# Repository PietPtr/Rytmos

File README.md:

# Rytmos

Very much experimental software for defining, rendering, synthesizing, and practicing single voice music notation using embedded graphics (e.g. on an SSD1306 128x64 OLED display)

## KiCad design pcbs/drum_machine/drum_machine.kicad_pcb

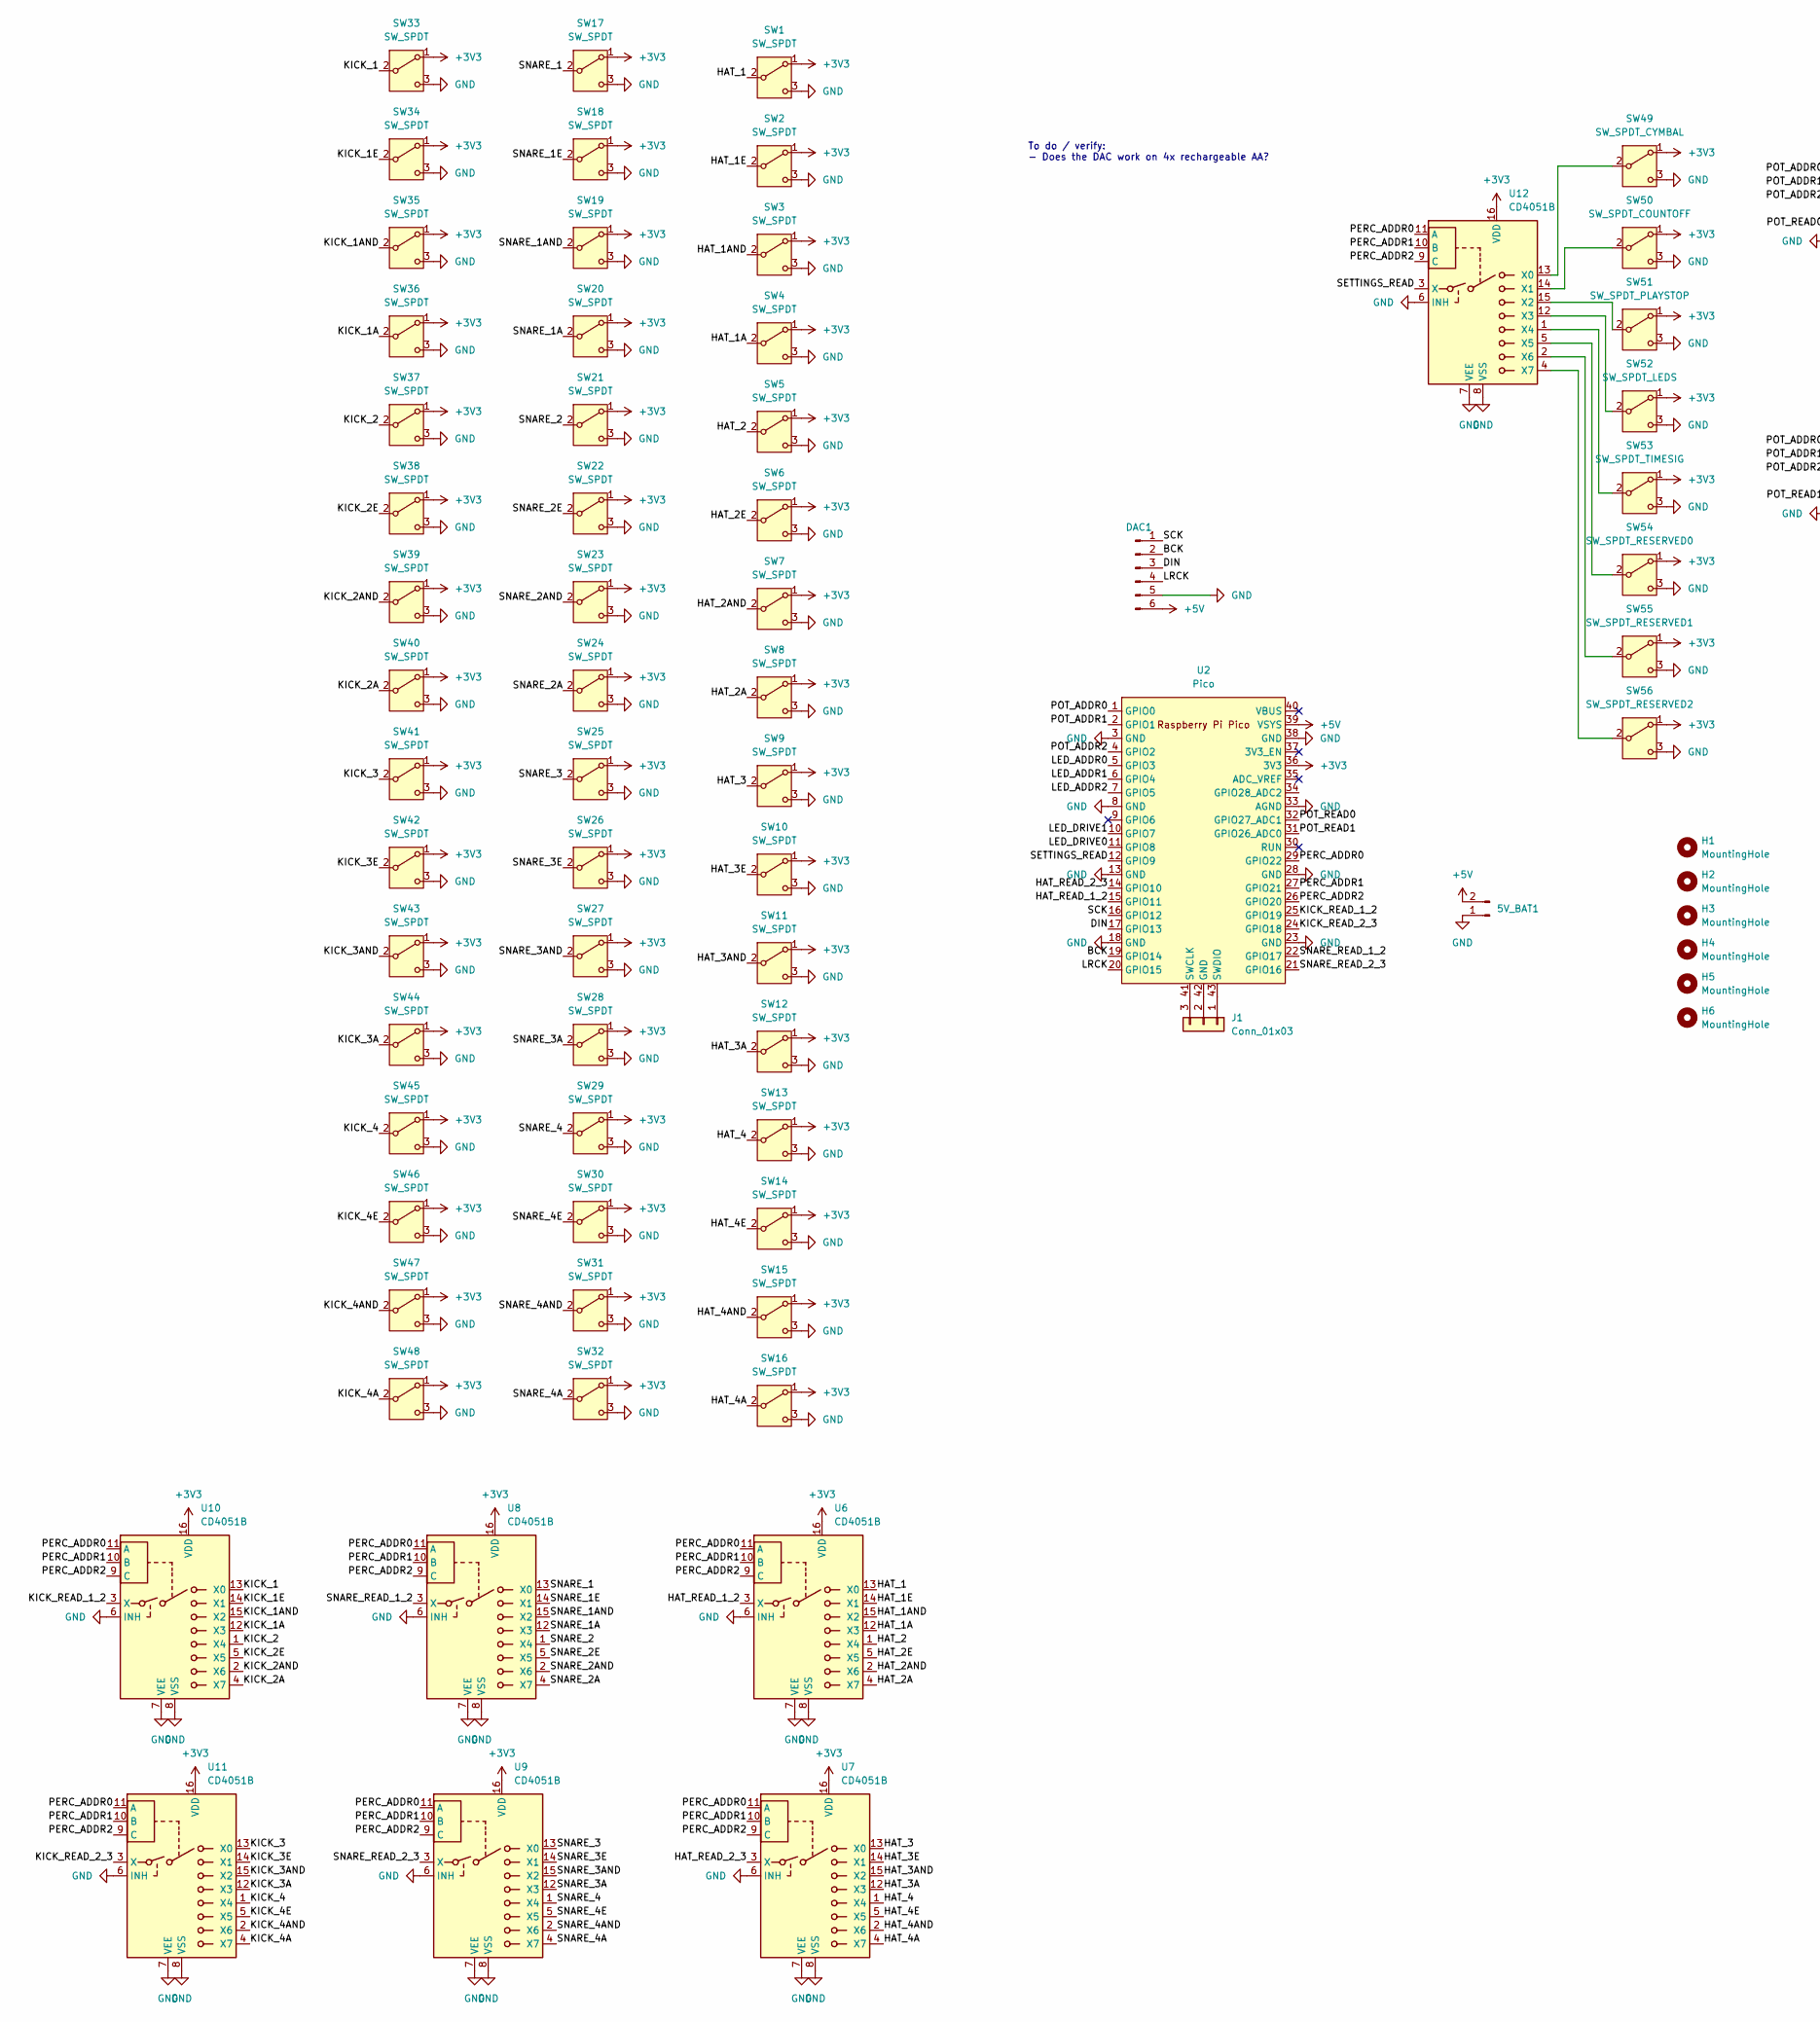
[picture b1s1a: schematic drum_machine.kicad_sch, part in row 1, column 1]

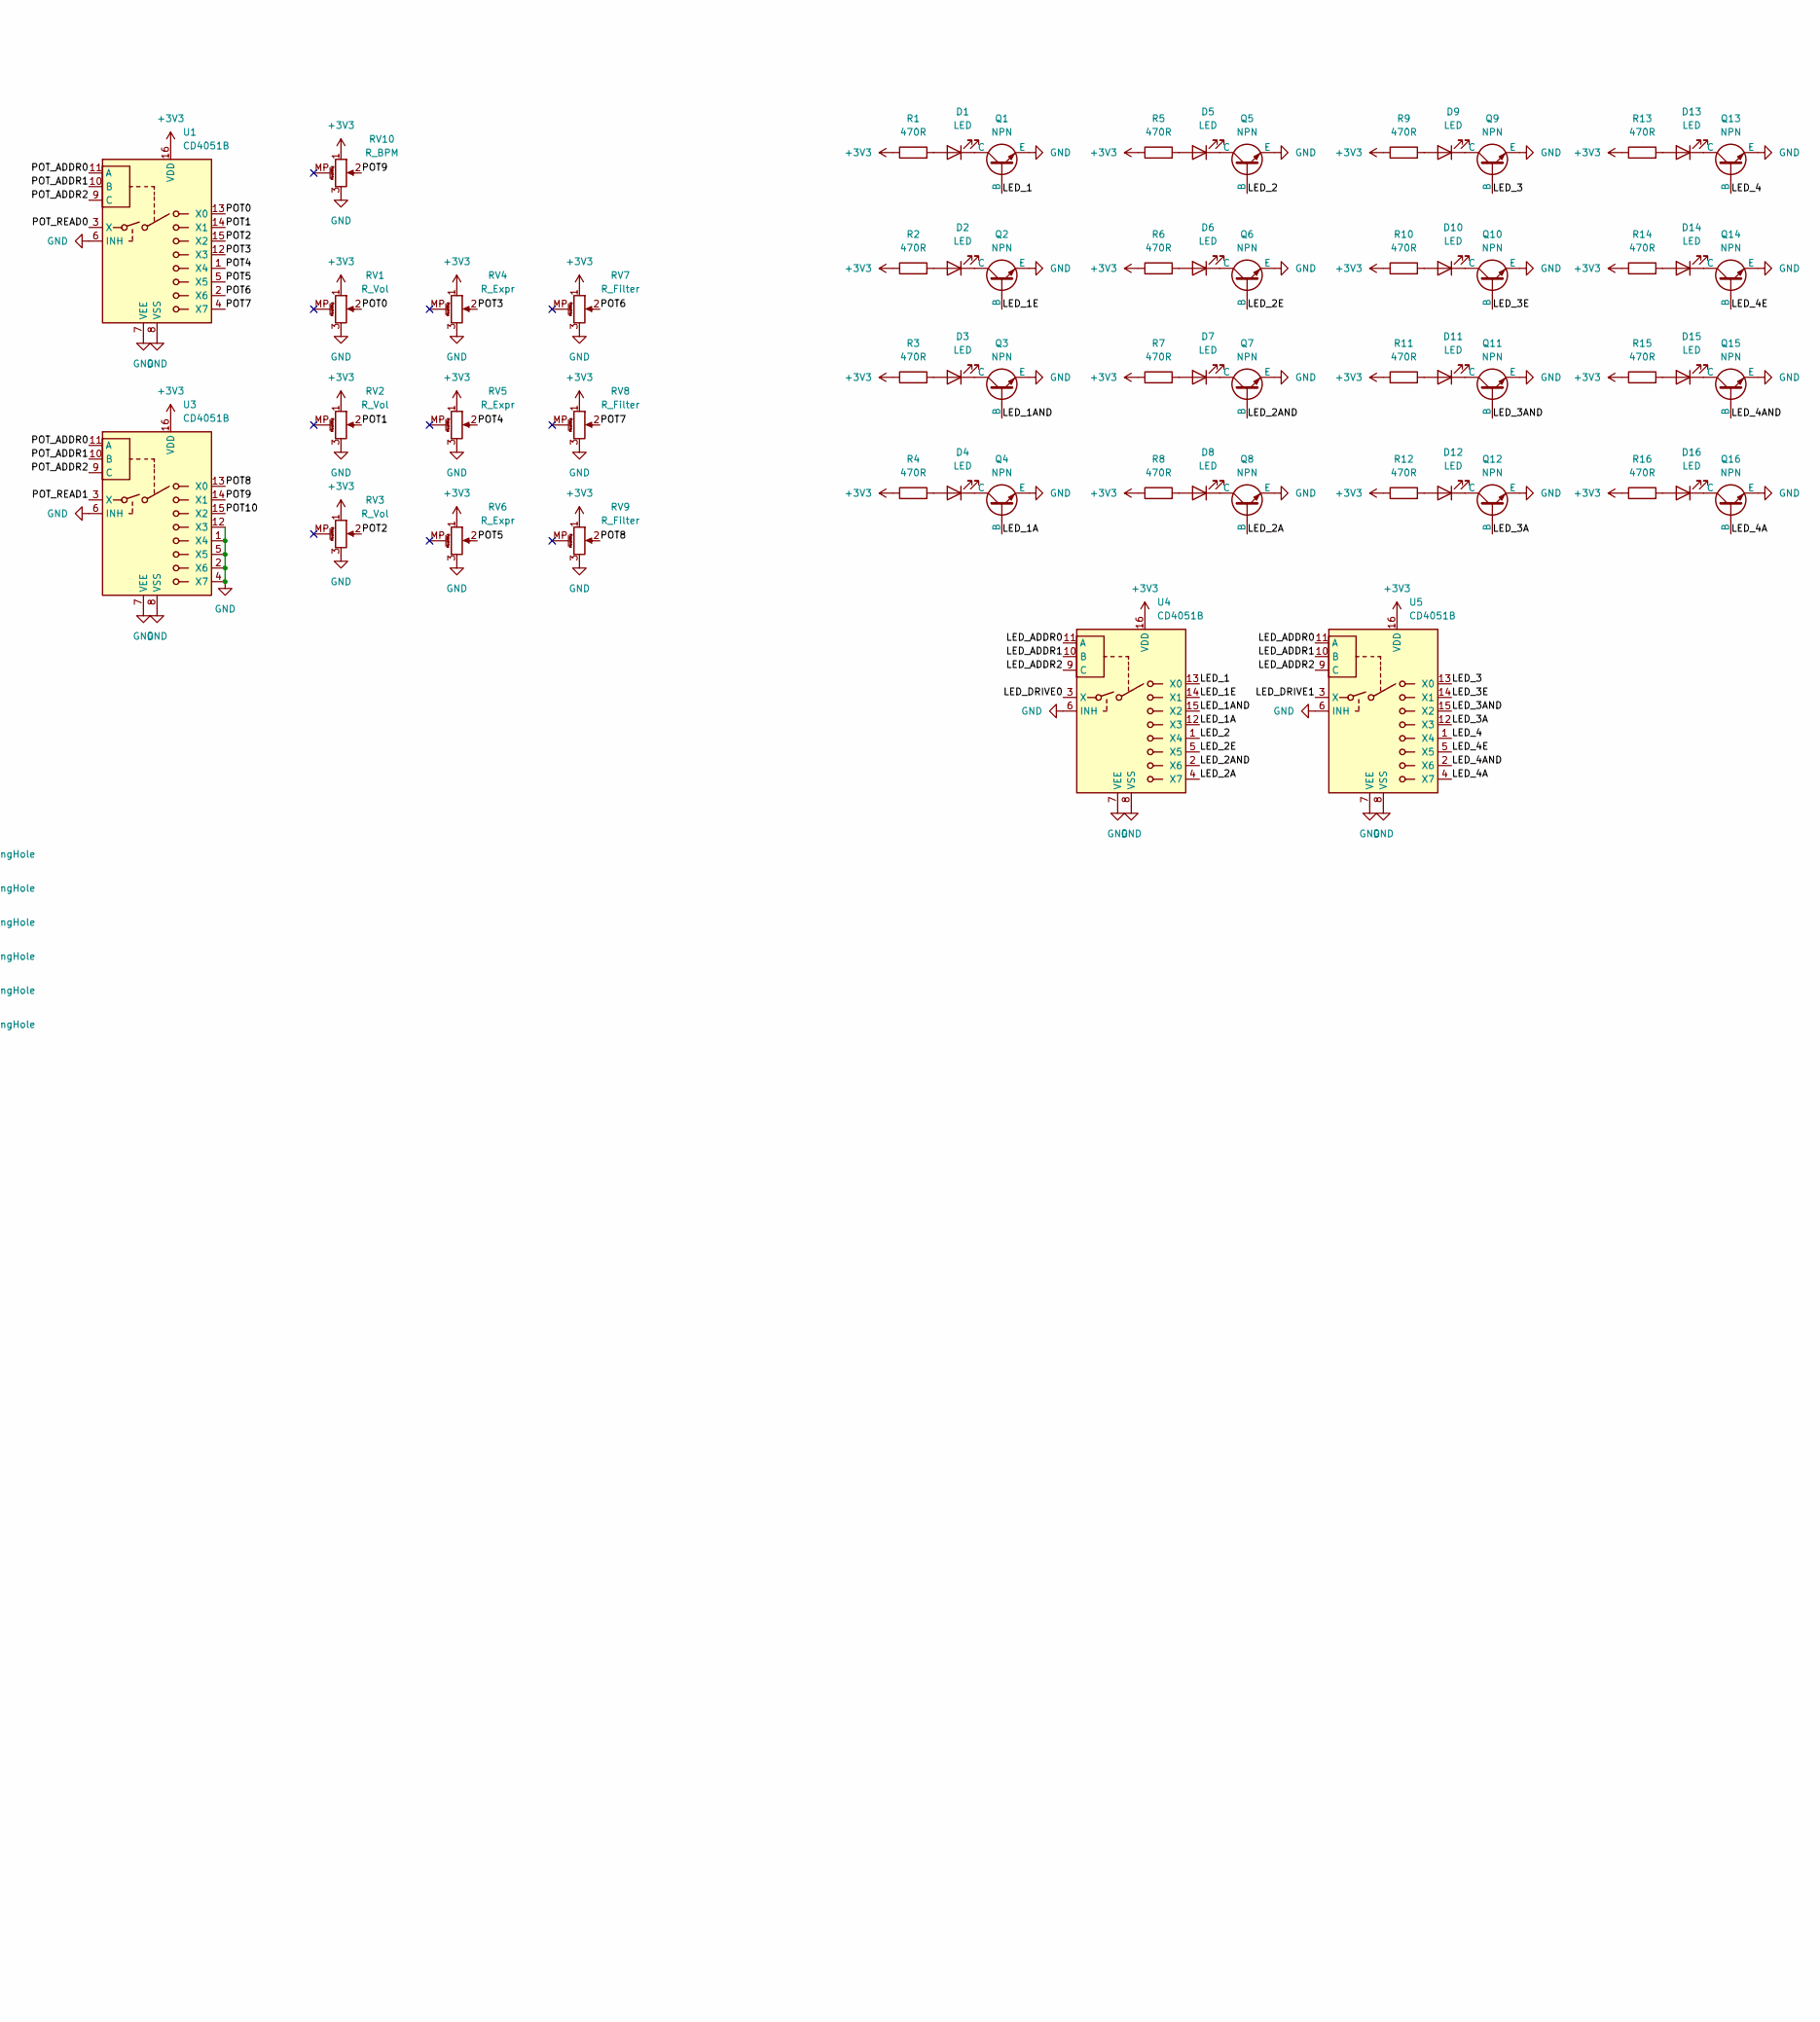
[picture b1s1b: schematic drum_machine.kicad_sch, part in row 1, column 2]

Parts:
5V_BAT1: Conn_01x02_Pin; PinSocket_1x02_P2.54mm_Vertical
D1, D2, D3, D4, D5, D6, D7, D8, D9, D10, D11, D12, D13, D14, D15, D16: LED; LED_D3.0mm
DAC1: DAC; PCM5102_BREAKOUT
H1, H2, H3, H4, H5, H6: MountingHole; MountingHole_2.7mm_M2.5
J1: Conn_01x03; PinSocket_1x03_P2.54mm_Vertical
Q1, Q2, Q3, Q4, Q5, Q6, Q7, Q8, Q9, Q10, Q11, Q12, Q13, Q14, Q15, Q16: NPN; TO-92L_Inline
R1, R2, R3, R4, R5, R6, R7, R8, R9, R10, R11, R12, R13, R14, R15, R16: 470R
RV1, RV2, RV3: R_Vol
RV4, RV5, RV6: R_Expr
RV7, RV8, RV9: R_Filter
RV10: R_BPM
SW1, SW2, SW3, SW4, SW5, SW6, SW7, SW8, SW9, SW10, SW11, SW12, SW13, SW14, SW15, SW16, SW17, SW18, SW19, SW20, SW21, SW22, SW23, SW24, SW25, SW26, SW27, SW28, SW29, SW30, SW31, SW32, SW33, SW34, SW35, SW36, SW37, SW38, SW39, SW40, SW41, SW42, SW43, SW44, SW45, SW46, SW47, SW48: SW_SPDT
SW49: SW_SPDT_CYMBAL
SW50: SW_SPDT_COUNTOFF
SW51: SW_SPDT_PLAYSTOP
SW52: SW_SPDT_LEDS
SW53: SW_SPDT_TIMESIG
SW54: SW_SPDT_RESERVED0
SW55: SW_SPDT_RESERVED1
SW56: SW_SPDT_RESERVED2
U1, U3, U4, U5, U6, U7, U8, U9, U10, U11, U12: CD4051B
U2: Pico; RPi_Pico_SMD_TH

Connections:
+3V3: R1.1, R2.1, R3.1, R4.1, R5.1, R6.1, R7.1, R8.1, R9.1, R10.1, R11.1, R12.1, R13.1, R14.1, R15.1, R16.1, RV1.1, RV2.1, RV3.1, RV4.1, RV5.1, RV6.1, RV7.1, RV8.1, RV9.1, RV10.1, SW1.1 (A), SW2.1 (A), SW3.1 (A), SW4.1 (A), SW5.1 (A), SW6.1 (A), SW7.1 (A), SW8.1 (A), SW9.1 (A), SW10.1 (A), SW11.1 (A), SW12.1 (A), SW13.1 (A), SW14.1 (A), SW15.1 (A), SW16.1 (A), SW17.1 (A), SW18.1 (A), SW19.1 (A), SW20.1 (A), SW21.1 (A), SW22.1 (A), SW23.1 (A), SW24.1 (A), SW25.1 (A), SW26.1 (A), SW27.1 (A), SW28.1 (A), SW29.1 (A), SW30.1 (A), SW31.1 (A), SW32.1 (A), SW33.1 (A), SW34.1 (A), SW35.1 (A), SW36.1 (A), SW37.1 (A), SW38.1 (A), SW39.1 (A), SW40.1 (A), SW41.1 (A), SW42.1 (A), SW43.1 (A), SW44.1 (A), SW45.1 (A), SW46.1 (A), SW47.1 (A), SW48.1 (A), SW49.1 (A), SW50.1 (A), SW51.1 (A), SW52.1 (A), SW53.1 (A), SW54.1 (A), SW55.1 (A), SW56.1 (A), U1.16 (VDD), U2.36 (3V3), U3.16 (VDD), U4.16 (VDD), U5.16 (VDD), U6.16 (VDD), U7.16 (VDD), U8.16 (VDD), U9.16 (VDD), U10.16 (VDD), U11.16 (VDD), U12.16 (VDD)
+5V: 5V_BAT1.2, DAC1.6, U2.39 (VSYS)
/BCK: DAC1.2, U2.19 (GPIO14)
/DIN: DAC1.3, U2.17 (GPIO13)
/HAT_1: SW1.2 (B), U6.13 (X0)
/HAT_1A: SW4.2 (B), U6.12 (X3)
/HAT_1AND: SW3.2 (B), U6.15 (X2)
/HAT_1E: SW2.2 (B), U6.14 (X1)
/HAT_2: SW5.2 (B), U6.1 (X4)
/HAT_2A: SW8.2 (B), U6.4 (X7)
/HAT_2AND: SW7.2 (B), U6.2 (X6)
/HAT_2E: SW6.2 (B), U6.5 (X5)
/HAT_3: SW9.2 (B), U7.13 (X0)
/HAT_3A: SW12.2 (B), U7.12 (X3)
/HAT_3AND: SW11.2 (B), U7.15 (X2)
/HAT_3E: SW10.2 (B), U7.14 (X1)
/HAT_4: SW13.2 (B), U7.1 (X4)
/HAT_4A: SW16.2 (B), U7.4 (X7)
/HAT_4AND: SW15.2 (B), U7.2 (X6)
/HAT_4E: SW14.2 (B), U7.5 (X5)
/HAT_READ_1_2: U2.15 (GPIO11), U6.3 (X)
/HAT_READ_2_3: U2.14 (GPIO10), U7.3 (X)
/KICK_1: SW33.2 (B), U10.13 (X0)
/KICK_1A: SW36.2 (B), U10.12 (X3)
/KICK_1AND: SW35.2 (B), U10.15 (X2)
/KICK_1E: SW34.2 (B), U10.14 (X1)
/KICK_2: SW37.2 (B), U10.1 (X4)
/KICK_2A: SW40.2 (B), U10.4 (X7)
/KICK_2AND: SW39.2 (B), U10.2 (X6)
/KICK_2E: SW38.2 (B), U10.5 (X5)
/KICK_3: SW41.2 (B), U11.13 (X0)
/KICK_3A: SW44.2 (B), U11.12 (X3)
/KICK_3AND: SW43.2 (B), U11.15 (X2)
/KICK_3E: SW42.2 (B), U11.14 (X1)
/KICK_4: SW45.2 (B), U11.1 (X4)
/KICK_4A: SW48.2 (B), U11.4 (X7)
/KICK_4AND: SW47.2 (B), U11.2 (X6)
/KICK_4E: SW46.2 (B), U11.5 (X5)
/KICK_READ_1_2: U2.25 (GPIO19), U10.3 (X)
/KICK_READ_2_3: U2.24 (GPIO18), U11.3 (X)
/LED_1: Q1.2 (B), U4.13 (X0)
/LED_1A: Q4.2 (B), U4.12 (X3)
/LED_1AND: Q3.2 (B), U4.15 (X2)
/LED_1E: Q2.2 (B), U4.14 (X1)
/LED_2: Q5.2 (B), U4.1 (X4)
/LED_2A: Q8.2 (B), U4.4 (X7)
/LED_2AND: Q7.2 (B), U4.2 (X6)
/LED_2E: Q6.2 (B), U4.5 (X5)
/LED_3: Q9.2 (B), U5.13 (X0)
/LED_3A: Q12.2 (B), U5.12 (X3)
/LED_3AND: Q11.2 (B), U5.15 (X2)
/LED_3E: Q10.2 (B), U5.14 (X1)
/LED_4: Q13.2 (B), U5.1 (X4)
/LED_4A: Q16.2 (B), U5.4 (X7)
/LED_4AND: Q15.2 (B), U5.2 (X6)
/LED_4E: Q14.2 (B), U5.5 (X5)
/LED_ADDR0: U2.5 (GPIO3), U4.11 (A), U5.11 (A)
/LED_ADDR1: U2.6 (GPIO4), U4.10 (B), U5.10 (B)
/LED_ADDR2: U2.7 (GPIO5), U4.9 (C), U5.9 (C)
/LED_DRIVE0: U2.11 (GPIO8), U4.3 (X)
/LED_DRIVE1: U2.10 (GPIO7), U5.3 (X)
/LRCK: DAC1.4, U2.20 (GPIO15)
/PERC_ADDR0: U2.29 (GPIO22), U6.11 (A), U7.11 (A), U8.11 (A), U9.11 (A), U10.11 (A), U11.11 (A), U12.11 (A)
/PERC_ADDR1: U2.27 (GPIO21), U6.10 (B), U7.10 (B), U8.10 (B), U9.10 (B), U10.10 (B), U11.10 (B), U12.10 (B)
/PERC_ADDR2: U2.26 (GPIO20), U6.9 (C), U7.9 (C), U8.9 (C), U9.9 (C), U10.9 (C), U11.9 (C), U12.9 (C)
/POT0: RV1.2, U1.13 (X0)
/POT1: RV2.2, U1.14 (X1)
/POT2: RV3.2, U1.15 (X2)
/POT3: RV4.2, U1.12 (X3)
/POT4: RV5.2, U1.1 (X4)
/POT5: RV6.2, U1.5 (X5)
/POT6: RV7.2, U1.2 (X6)
/POT7: RV8.2, U1.4 (X7)
/POT8: RV9.2, U3.13 (X0)
/POT9: RV10.2, U3.14 (X1)
/POT10: U3.15 (X2)
/POT_ADDR0: U1.11 (A), U2.1 (GPIO0), U3.11 (A)
/POT_ADDR1: U1.10 (B), U2.2 (GPIO1), U3.10 (B)
/POT_ADDR2: U1.9 (C), U2.4 (GPIO2), U3.9 (C)
/POT_READ0: U1.3 (X), U2.32 (GPIO27_ADC1)
/POT_READ1: U2.31 (GPIO26_ADC0), U3.3 (X)
/SCK: DAC1.1, U2.16 (GPIO12)
/SETTINGS_READ: U2.12 (GPIO9), U12.3 (X)
/SNARE_1: SW17.2 (B), U8.13 (X0)
/SNARE_1A: SW20.2 (B), U8.12 (X3)
/SNARE_1AND: SW19.2 (B), U8.15 (X2)
/SNARE_1E: SW18.2 (B), U8.14 (X1)
/SNARE_2: SW21.2 (B), U8.1 (X4)
/SNARE_2A: SW24.2 (B), U8.4 (X7)
/SNARE_2AND: SW23.2 (B), U8.2 (X6)
/SNARE_2E: SW22.2 (B), U8.5 (X5)
/SNARE_3: SW25.2 (B), U9.13 (X0)
/SNARE_3A: SW28.2 (B), U9.12 (X3)
/SNARE_3AND: SW27.2 (B), U9.15 (X2)
/SNARE_3E: SW26.2 (B), U9.14 (X1)
/SNARE_4: SW29.2 (B), U9.1 (X4)
/SNARE_4A: SW32.2 (B), U9.4 (X7)
/SNARE_4AND: SW31.2 (B), U9.2 (X6)
/SNARE_4E: SW30.2 (B), U9.5 (X5)
/SNARE_READ_1_2: U2.22 (GPIO17), U8.3 (X)
/SNARE_READ_2_3: U2.21 (GPIO16), U9.3 (X)
GND: 5V_BAT1.1, DAC1.5, Q1.3 (E), Q2.3 (E), Q3.3 (E), Q4.3 (E), Q5.3 (E), Q6.3 (E), Q7.3 (E), Q8.3 (E), Q9.3 (E), Q10.3 (E), Q11.3 (E), Q12.3 (E), Q13.3 (E), Q14.3 (E), Q15.3 (E), Q16.3 (E), RV1.3, RV2.3, RV3.3, RV4.3, RV5.3, RV6.3, RV7.3, RV8.3, RV9.3, RV10.3, SW1.3 (C), SW2.3 (C), SW3.3 (C), SW4.3 (C), SW5.3 (C), SW6.3 (C), SW7.3 (C), SW8.3 (C), SW9.3 (C), SW10.3 (C), SW11.3 (C), SW12.3 (C), SW13.3 (C), SW14.3 (C), SW15.3 (C), SW16.3 (C), SW17.3 (C), SW18.3 (C), SW19.3 (C), SW20.3 (C), SW21.3 (C), SW22.3 (C), SW23.3 (C), SW24.3 (C), SW25.3 (C), SW26.3 (C), SW27.3 (C), SW28.3 (C), SW29.3 (C), SW30.3 (C), SW31.3 (C), SW32.3 (C), SW33.3 (C), SW34.3 (C), SW35.3 (C), SW36.3 (C), SW37.3 (C), SW38.3 (C), SW39.3 (C), SW40.3 (C), SW41.3 (C), SW42.3 (C), SW43.3 (C), SW44.3 (C), SW45.3 (C), SW46.3 (C), SW47.3 (C), SW48.3 (C), SW49.3 (C), SW50.3 (C), SW51.3 (C), SW52.3 (C), SW53.3 (C), SW54.3 (C), SW55.3 (C), SW56.3 (C), U1.6 (INH), U1.7 (VEE), U1.8 (VSS), U2.3 (GND), U2.8 (GND), U2.13 (GND), U2.18 (GND), U2.23 (GND), U2.28 (GND), U2.33 (AGND), U2.38 (GND), U3.1 (X4), U3.2 (X6), U3.4 (X7), U3.5 (X5), U3.6 (INH), U3.7 (VEE), U3.8 (VSS), U3.12 (X3), U4.6 (INH), U4.7 (VEE), U4.8 (VSS), U5.6 (INH), U5.7 (VEE), U5.8 (VSS), U6.6 (INH), U6.7 (VEE), U6.8 (VSS), U7.6 (INH), U7.7 (VEE), U7.8 (VSS), U8.6 (INH), U8.7 (VEE), U8.8 (VSS), U9.6 (INH), U9.7 (VEE), U9.8 (VSS), U10.6 (INH), U10.7 (VEE), U10.8 (VSS), U11.6 (INH), U11.7 (VEE), U11.8 (VSS), U12.6 (INH), U12.7 (VEE), U12.8 (VSS)
unnamed: D1.2 (A), R1.2
unnamed: D1.1 (K), Q1.1 (C)
unnamed: D2.2 (A), R2.2
unnamed: D2.1 (K), Q2.1 (C)
unnamed: D3.2 (A), R3.2
unnamed: D3.1 (K), Q3.1 (C)
unnamed: D4.2 (A), R4.2
unnamed: D4.1 (K), Q4.1 (C)
unnamed: D5.2 (A), R5.2
unnamed: D5.1 (K), Q5.1 (C)
unnamed: D6.2 (A), R6.2
unnamed: D6.1 (K), Q6.1 (C)
unnamed: D7.2 (A), R7.2
unnamed: D7.1 (K), Q7.1 (C)
unnamed: D8.2 (A), R8.2
unnamed: D8.1 (K), Q8.1 (C)
unnamed: D9.2 (A), R9.2
unnamed: D9.1 (K), Q9.1 (C)
unnamed: D10.2 (A), R10.2
unnamed: D10.1 (K), Q10.1 (C)
unnamed: D11.2 (A), R11.2
unnamed: D11.1 (K), Q11.1 (C)
unnamed: D12.2 (A), R12.2
unnamed: D12.1 (K), Q12.1 (C)
unnamed: D13.2 (A), R13.2
unnamed: D13.1 (K), Q13.1 (C)
unnamed: D14.2 (A), R14.2
unnamed: D14.1 (K), Q14.1 (C)
unnamed: D15.2 (A), R15.2
unnamed: D15.1 (K), Q15.1 (C)
unnamed: D16.2 (A), R16.2
unnamed: D16.1 (K), Q16.1 (C)
unnamed: J1.1, U2.43 (SWDIO)
unnamed: J1.2, U2.42 (GND)
unnamed: J1.3, U2.41 (SWCLK)
unnamed: SW49.2 (B), U12.13 (X0)
unnamed: SW50.2 (B), U12.14 (X1)
unnamed: SW51.2 (B), U12.15 (X2)
unnamed: SW52.2 (B), U12.12 (X3)
unnamed: SW53.2 (B), U12.1 (X4)
unnamed: SW54.2 (B), U12.5 (X5)
unnamed: SW55.2 (B), U12.2 (X6)
unnamed: SW56.2 (B), U12.4 (X7)

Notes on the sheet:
To do / verify: - Does the DAC work on 4x rechargeable AA?

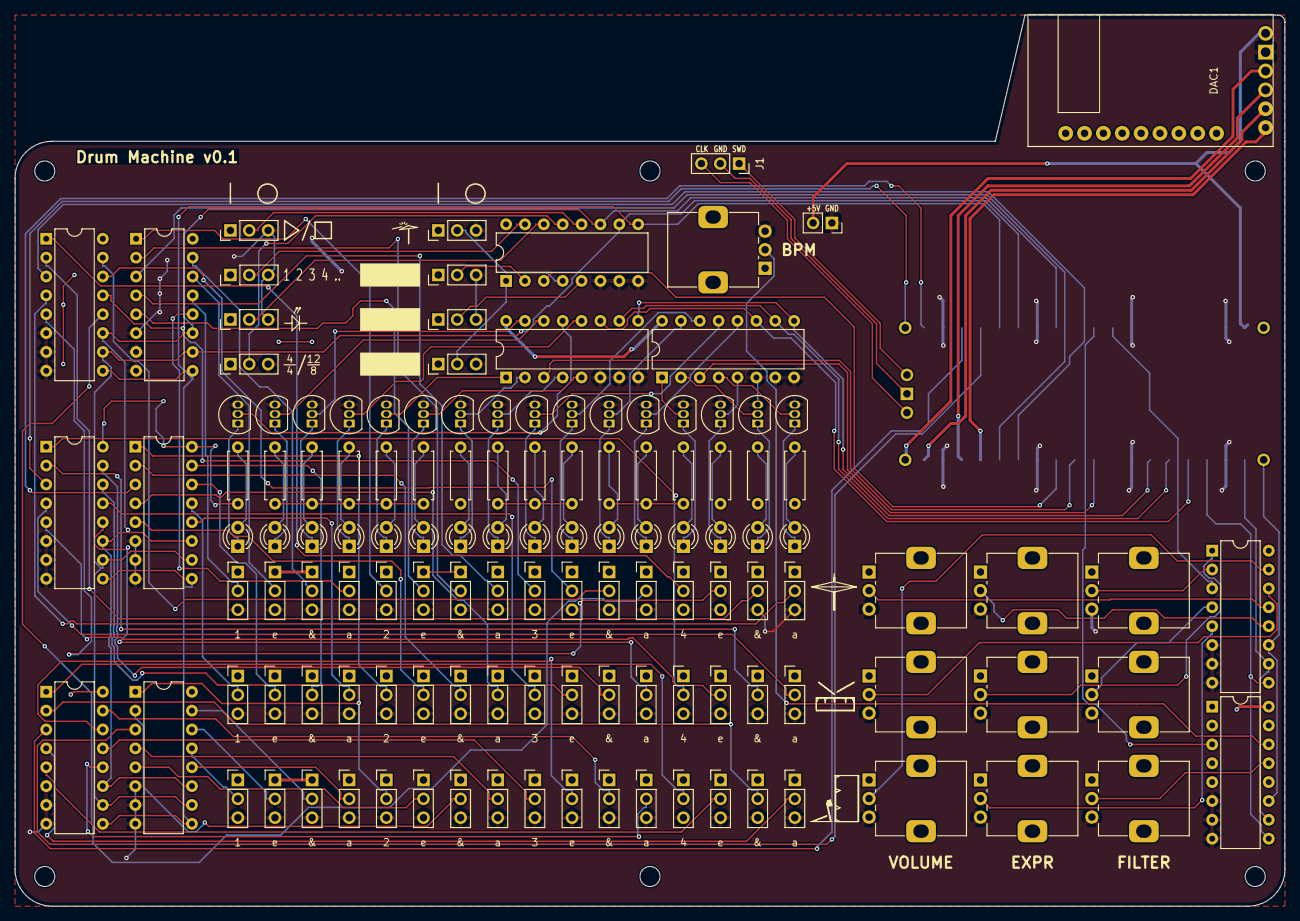
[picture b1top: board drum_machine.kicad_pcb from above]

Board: 2 copper layers, 171.0 x 120.0 mm, 135 parts (1 on the bottom side), 144 nets.

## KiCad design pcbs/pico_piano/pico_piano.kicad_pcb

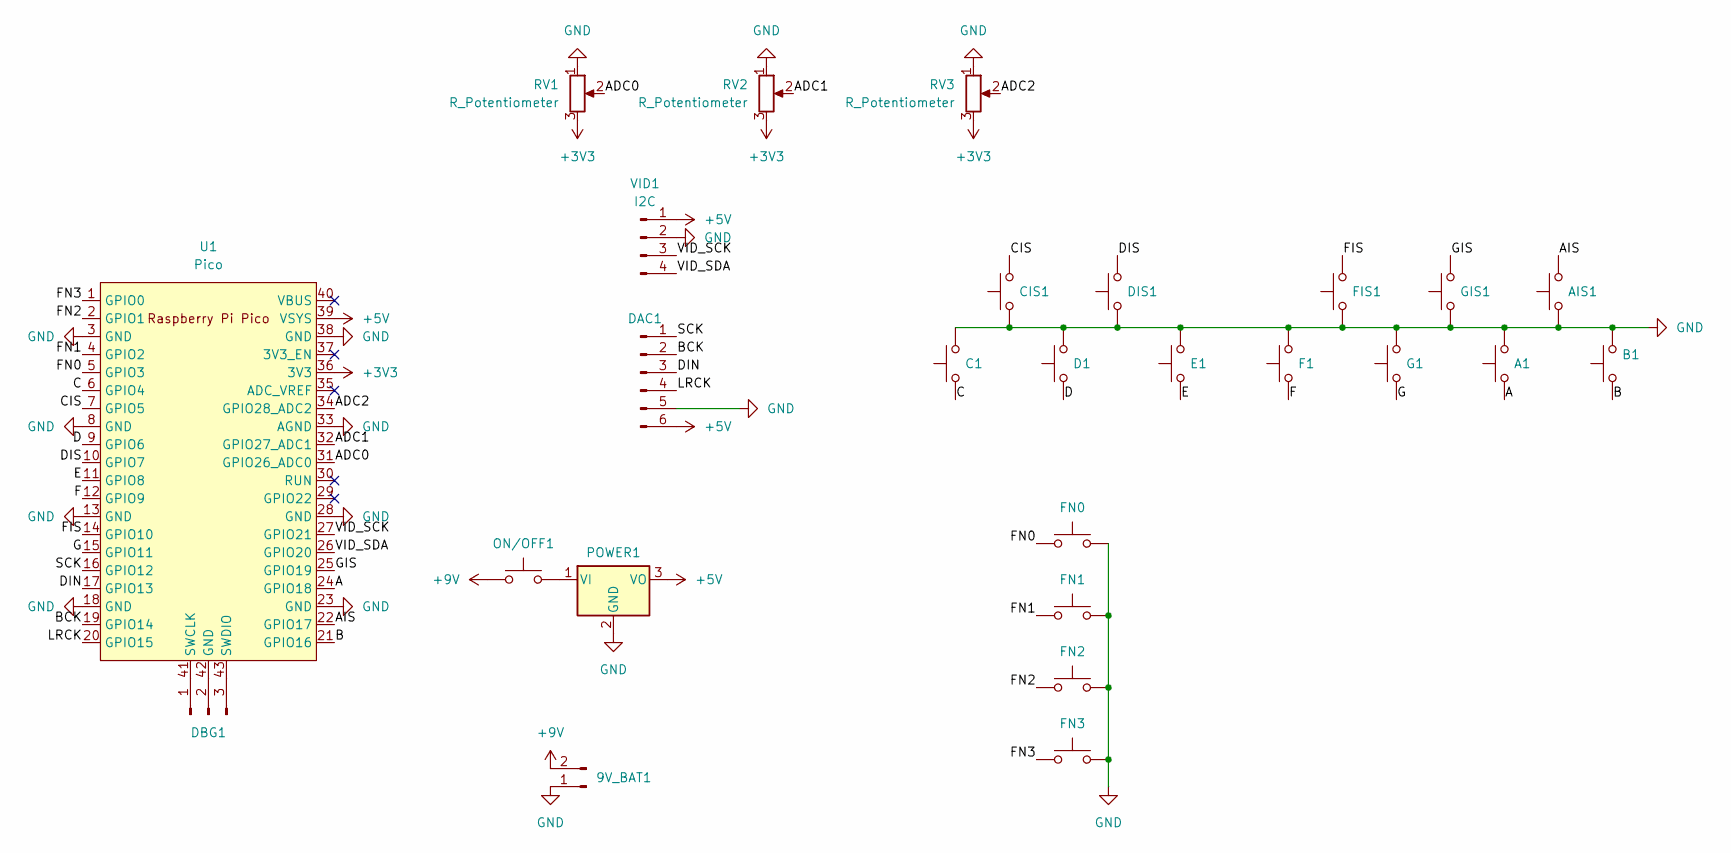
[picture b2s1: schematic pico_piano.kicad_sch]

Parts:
9V_BAT1: Conn_01x02_Pin; PinSocket_1x02_P2.54mm_Vertical
A1: SW_Push; KAILH_MUTE
AIS1: SW_Push; KAILH_MUTE
B1: SW_Push; KAILH_MUTE
C1: SW_Push; KAILH_MUTE
CIS1: SW_Push; KAILH_MUTE
D1: SW_Push; KAILH_MUTE
DAC1: DAC; PCM5102_BREAKOUT
DBG1: Conn_01x03_Pin; PinSocket_1x03_P2.54mm_Vertical
DIS1: SW_Push; KAILH_MUTE
E1: SW_Push; KAILH_MUTE
F1: SW_Push; KAILH_MUTE
FIS1: SW_Push; KAILH_MUTE
FN0, FN1, FN2, FN3: SW_Push; KAILH_MUTE
G1: SW_Push; KAILH_MUTE
GIS1: SW_Push; KAILH_MUTE
ON/OFF1: SW_Push; PinHeader_1x03_P2.54mm_Vertical
POWER1: LM7805_TO220; TO-220-3_Horizontal_TabDown
RV1, RV2, RV3: R_Potentiometer; PinHeader_1x03_P2.54mm_Vertical
U1: Pico; RPi_Pico_SMD_TH
VID1: I2C; PinHeader_1x04_P2.54mm_Vertical

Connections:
+3V3: RV1.3, RV2.3, RV3.3, U1.36 (3V3)
+5V: DAC1.6, POWER1.3 (VO), U1.39 (VSYS), VID1.1
+9V: 9V_BAT1.2, ON/OFF1.1
/A: A1.1, U1.24 (GPIO18)
/ADC0: RV1.2, U1.31 (GPIO26_ADC0)
/ADC1: RV2.2, U1.32 (GPIO27_ADC1)
/ADC2: RV3.2, U1.34 (GPIO28_ADC2)
/AIS: AIS1.2, U1.22 (GPIO17)
/B: B1.1, U1.21 (GPIO16)
/BCK: DAC1.2, U1.19 (GPIO14)
/C: C1.1, U1.6 (GPIO4)
/CIS: CIS1.2, U1.7 (GPIO5)
/D: D1.1, U1.9 (GPIO6)
/DIN: DAC1.3, U1.17 (GPIO13)
/DIS: DIS1.2, U1.10 (GPIO7)
/E: E1.1, U1.11 (GPIO8)
/F: F1.1, U1.12 (GPIO9)
/FIS: FIS1.2, U1.14 (GPIO10)
/FN0: FN0.1, U1.5 (GPIO3)
/FN1: FN1.1, U1.4 (GPIO2)
/FN2: FN2.1, U1.2 (GPIO1)
/FN3: FN3.1, U1.1 (GPIO0)
/G: G1.1, U1.15 (GPIO11)
/GIS: GIS1.2, U1.25 (GPIO19)
/LRCK: DAC1.4, U1.20 (GPIO15)
/SCK: DAC1.1, U1.16 (GPIO12)
/VID_SCK: U1.27 (GPIO21), VID1.3
/VID_SDA: U1.26 (GPIO20), VID1.4
GND: 9V_BAT1.1, A1.2, AIS1.1, B1.2, C1.2, CIS1.1, D1.2, DAC1.5, DIS1.1, E1.2, F1.2, FIS1.1, FN0.2, FN1.2, FN2.2, FN3.2, G1.2, GIS1.1, POWER1.2 (GND), RV1.1, RV2.1, RV3.1, U1.3 (GND), U1.8 (GND), U1.13 (GND), U1.18 (GND), U1.23 (GND), U1.28 (GND), U1.33 (AGND), U1.38 (GND), VID1.2
unnamed: DBG1.1, U1.41 (SWCLK)
unnamed: DBG1.2, U1.42 (GND)
unnamed: DBG1.3, U1.43 (SWDIO)
unnamed: ON/OFF1.2, POWER1.1 (VI)

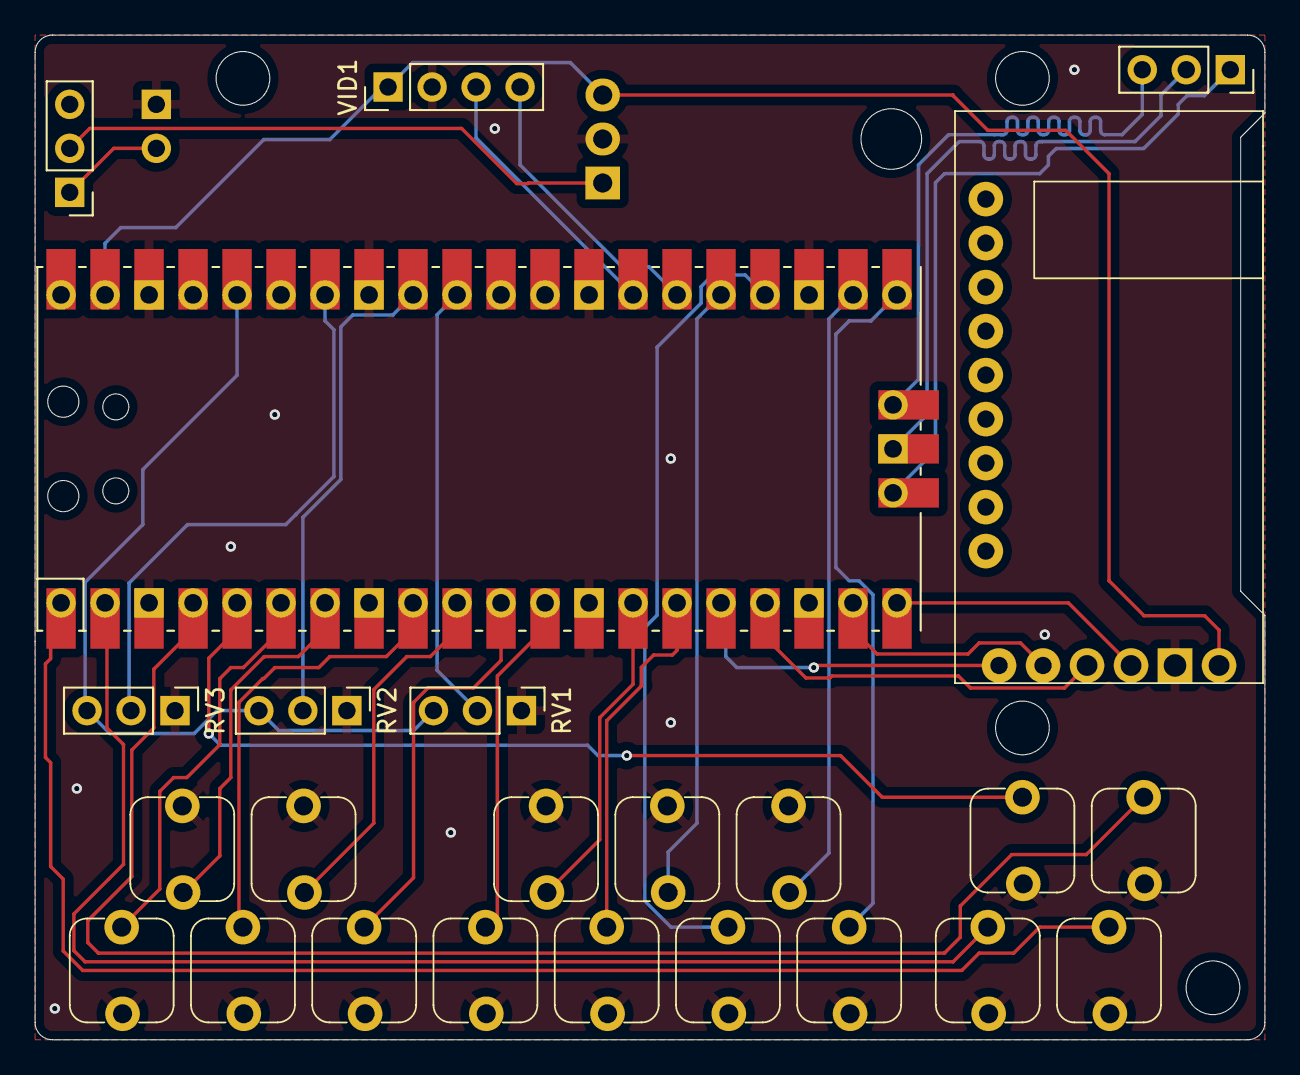
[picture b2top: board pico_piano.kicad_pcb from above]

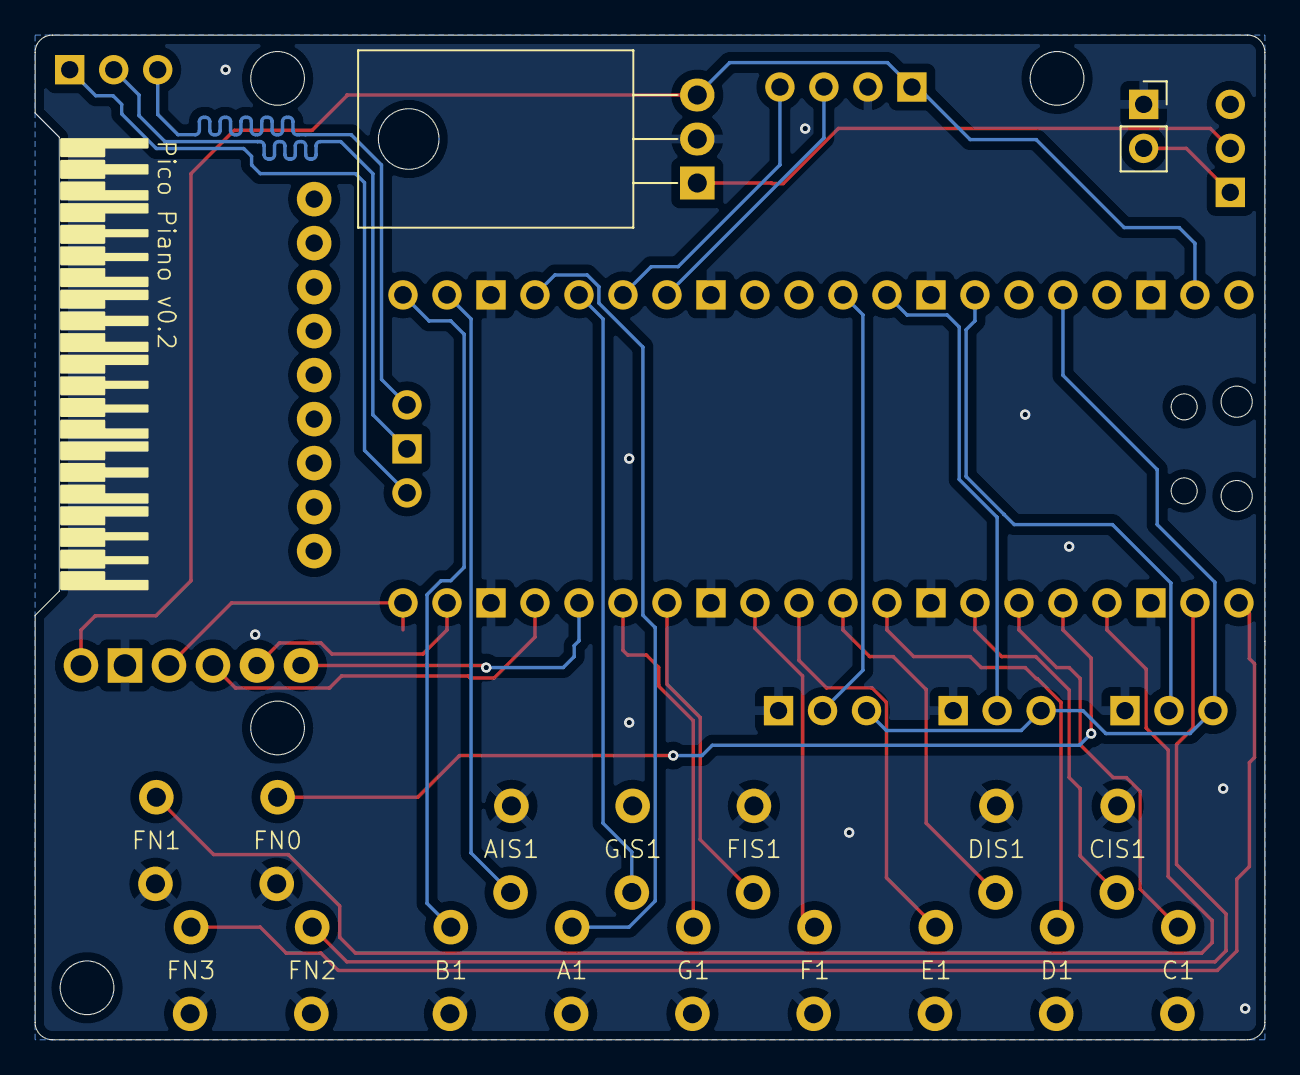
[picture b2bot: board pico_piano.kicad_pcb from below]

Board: 2 copper layers, 71.0 x 58.0 mm, 26 parts (2 on the bottom side), 33 nets.

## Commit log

2024-07-25 initial
2024-08-22 Add ties
2024-08-22 Setup synth crate
2024-08-22 Add play analysis
2024-08-22 add rytmos scribe
2024-08-22 add interactive demo
2024-08-22 Move rytmos to rytmos-engrave
2024-09-07 Add pico demo (Triangle wave)
2024-09-07 Add more synths
2024-09-08 Run synth in seperate thread
2024-09-08 Abstract interface out of demo
2024-09-09 Add getting synth commands from synth controller
2024-09-10 Add metronome synth
2024-09-17 Use synth
2024-10-04 Add SetAttack command
2024-10-13 Add fret/pluck logic
2024-10-13 WIP: menu
2024-10-15 Menus
2024-10-18 Add stuff i guess
2024-10-22 Add stuff
2024-10-25 Implement metronome ticks in synth controller
2024-10-25 Refactor metronome synth, add master synth
2024-10-27 Add interface to pico main.rs
2024-11-02 Add hopefully correct driving of the synth to pico
2024-11-02 Add PCB project files
2024-11-08 WIP: real hardware tests
2024-11-09 Tests with scope
2024-11-09 Make bit clock 50% duty cycle
2024-11-10 Working DAC
2024-11-10 Introduce fixed point (breaks most synths)
2024-11-10 Speed up sawtooth synth
2024-11-10 Precompute frequencies
2024-11-17 Pico Piano PCB changes
2024-11-17 Split rytmos-pico in several crates
2024-11-17 Add increment lookup tables
2024-11-17 Add buttons to piano
2024-11-17 Refactor frequencies
2024-11-17 Add fn buttons, clean up pico piano main.rs
2024-11-17 Update pico piano PCB
2024-11-19 Add attack function
2024-11-26 Convert sine table
2024-11-27 Add sine wave
2024-11-27 Apply sine synth in pico piano and use velocity
2024-11-27 Update Pico Piano PCB components
2024-11-28 Sine tests
2024-11-28 Route tracks on pico piano v0.2
2024-12-01 Clean up most synths
2024-12-01 Verify other pins work for i2s
2024-12-02 Add effects
2024-12-03 Rework Synth and Effect traits
2024-12-04 WIP: hw benchmark
2024-12-04 Order v0.2 of pico piano PCB
2024-12-04 Add benchmarks in i2s_testbed crate
2024-12-19 Add SMD pico footprint
2025-01-16 Add polyphonic synth
2025-03-05 Add things
2025-03-05 Add drum machine
2025-03-08 Add drum synth
2025-03-09 Start drum machine IO reading
2025-03-09 Route drum machine
2025-03-09 Connect LED addresses
2025-03-11 Add sequencer
2025-03-18 Add drum machine software
2025-03-19 Order drum_machine v0.1
2025-03-22 Add chord feature to pico piano
2025-04-02 Drum Machine Bringup, refactor sample synth
2025-04-09 Fixes after real hw tests
2025-04-09 Add support for more uses of the pico piano in one binary
2025-04-15 Add applying settings to chord loop interface
2025-04-16 Add midi pedals
2025-04-18 Add MIDI pedals PCB
2025-04-19 Order MIDI pedals v0.1
2025-05-03 Add practice bass initial code
2025-05-03 Move polypicophonic product functionality out of embedded context
2025-05-03 Web experiments
2025-05-04 Connect Dioxus frontend to interface
2025-05-04 Wasm Audio attempt
2025-05-04 Finish WASM audio attempt
2025-05-04 Connect WASM audio to synth, connect dioxus to WASM audio
2025-05-04 Style like the picopiano
2025-05-05 Attach key listeners to window instead of div
2025-05-05 Hold shift for help
2025-05-13 Change font, add touch, init audio automatically
2025-05-17 Rework wasm audio
2025-05-23 Add Frequency CommandMessage for synths
2025-06-15 Add amplify / distort effect
2025-06-19 Add Reconfigure command
2025-10-31 Add frequency support to sawtooth
2025-10-31 Solve some warnings
2025-11-16 Trigger debouncers earlier
